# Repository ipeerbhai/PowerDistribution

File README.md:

# PowerDistribution
This design is for a small wiring board to provide power to a robotic rover.

It's designed in 3 sections.

## Part 1: High Current ESC Pads ##
This part is 3 thick traces without masking to push high voltage/current power in a short segment.  It is completely unfused, and should be pushed to a smart, power-hungry board like an ODrive.  The lack of masks is to enable solder as a wire for high-current and voltage use cases.

## Part 2: Battery Monitoring ##
This part has 2 SMD resistors in a simple voltage divider circuit.  The resistor values chosen are 22M-ohm (RMCF0805FT22M0) and 1M-ohm(RC0805FR-071ML.  This enables voltage detection on a Teensy 4.1 from 0 to 50V.

## Part 3: Switch and buck converters ##
A large swtich pad for a single pole, single throw switch,
a small pad buck converter for a raspberry pi or other SBC, and 2 large pads for very high-current buck converters for Star-power servos.
For the switch, Amazon part number: B078KBC5VH
For the RPi Buck converter, Amazon part number: B079N9BFZC
For the Star-Power converter, Amazon part number: B0819Y8PJZ

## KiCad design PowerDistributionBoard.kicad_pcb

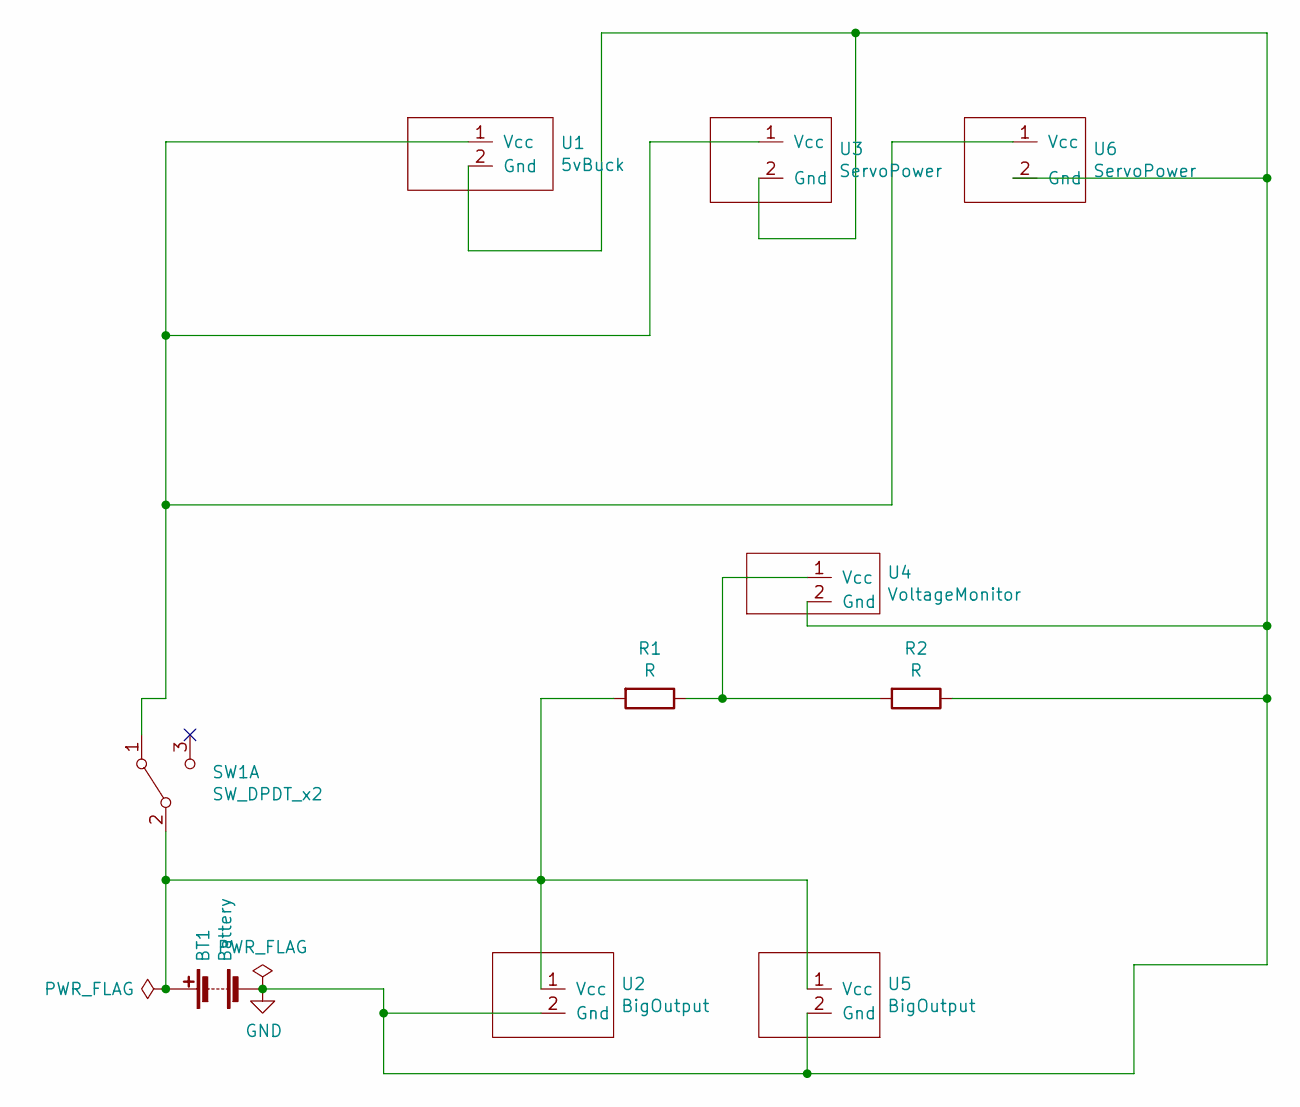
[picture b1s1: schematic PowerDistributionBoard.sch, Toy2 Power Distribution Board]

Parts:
BT1: Battery; BigOutput
R1, R2: R; R_0805_2012Metric_Pad1.15x1.40mm_HandSolder
SW1: SW_DPDT_x2; BigSwitch
U1: 5vBuck; SmallPower
U2, U5: BigOutput
U3, U6: ServoPower; BigOutput
U4: VoltageMonitor; PinHeader_1x02_P2.54mm_Vertical

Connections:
GND: BT1.2 (-), R2.1, U1.2 (Gnd), U2.2 (Gnd), U3.2 (Gnd), U4.2 (Gnd), U5.2 (Gnd), U6.2 (Gnd)
unnamed: BT1.1 (+), R1.2, SW1.2 (B), U2.1 (Vcc), U5.1 (Vcc)
unnamed: R1.1, R2.2, U4.1 (Vcc)
unnamed: SW1.1 (A), U1.1 (Vcc), U3.1 (Vcc), U6.1 (Vcc)

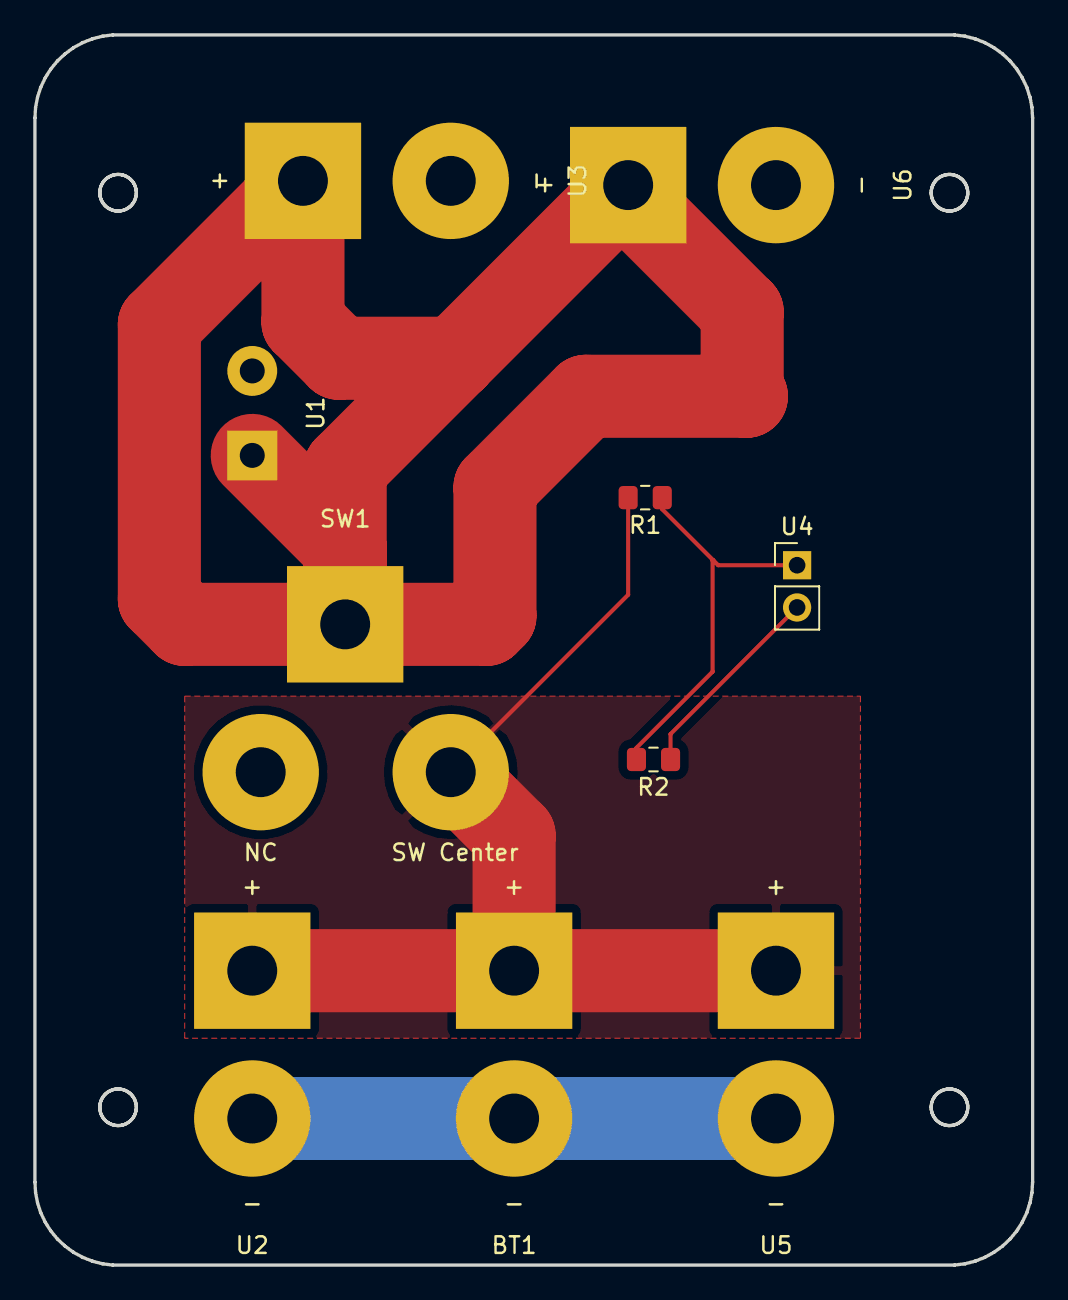
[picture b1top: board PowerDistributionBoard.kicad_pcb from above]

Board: 2 copper layers, 60.0 x 74.0 mm, 10 parts (0 on the bottom side), 4 nets.

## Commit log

2020-08-31 Moving simple power design to public, open-source project.
